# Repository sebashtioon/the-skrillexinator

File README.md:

# the-skrillexinator
a mini rave in your room, brought to you by esp32 and leds

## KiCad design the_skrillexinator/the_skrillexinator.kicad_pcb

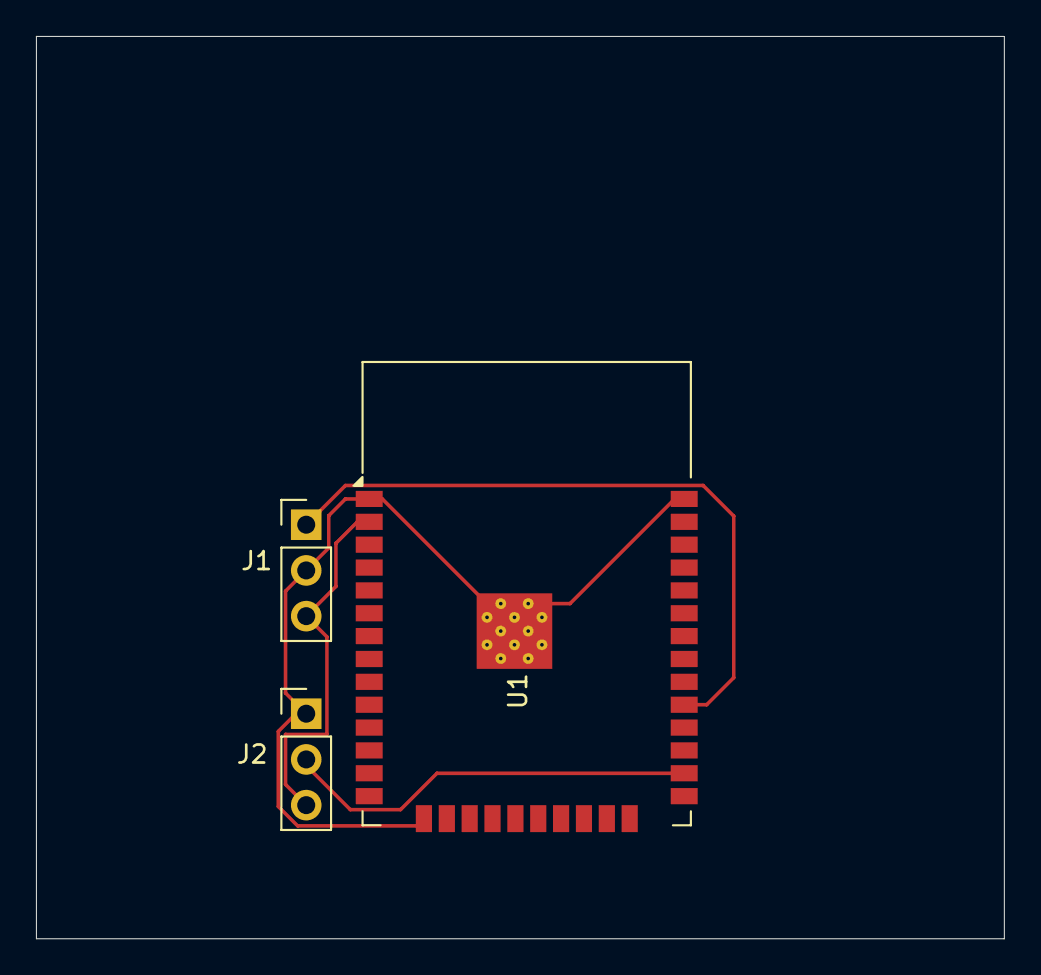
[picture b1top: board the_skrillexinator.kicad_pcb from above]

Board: 2 copper layers, 53.8 x 50.1 mm, 3 parts (0 on the bottom side), 4 nets.

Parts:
J1, J2: Conn_01x03; PinHeader_1x03_P2.54mm_Vertical
U1: ESP32-WROOM-32

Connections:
+3.3V: J1.3, J2.3, U1.2 (VDD)
GND: J1.2, J2.1, U1.1 (GND), U1.15 (GND), U1.38 (GND), U1.39 (GND)
unnamed: J1.1, U1.29 (IO5)
unnamed: J2.2, U1.26 (IO4)

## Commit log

2026-04-14 add shit
2026-04-14 add resistor shit
2026-04-14 add di powa
2026-04-14 add di EVREYTHING
2026-04-14 add di pcb
2026-04-14 skibidi
2026-04-14 goog
2026-04-14 more pcbing
2026-04-14 wire that bi
2026-04-14 help
2026-04-14 HOORAHHHHH
2026-04-14 SIKIB
2026-04-14 ting
2026-04-14 PLOT
2026-04-14 idk gng
2026-04-14 chibs
